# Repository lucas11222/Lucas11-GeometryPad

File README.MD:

# Lucas11 GeometryPad
An HackPad for the popular game Geometry dash. (i love gd colonge)
## Made for Highway (Hackpad)
# Heres a photo of the pcb

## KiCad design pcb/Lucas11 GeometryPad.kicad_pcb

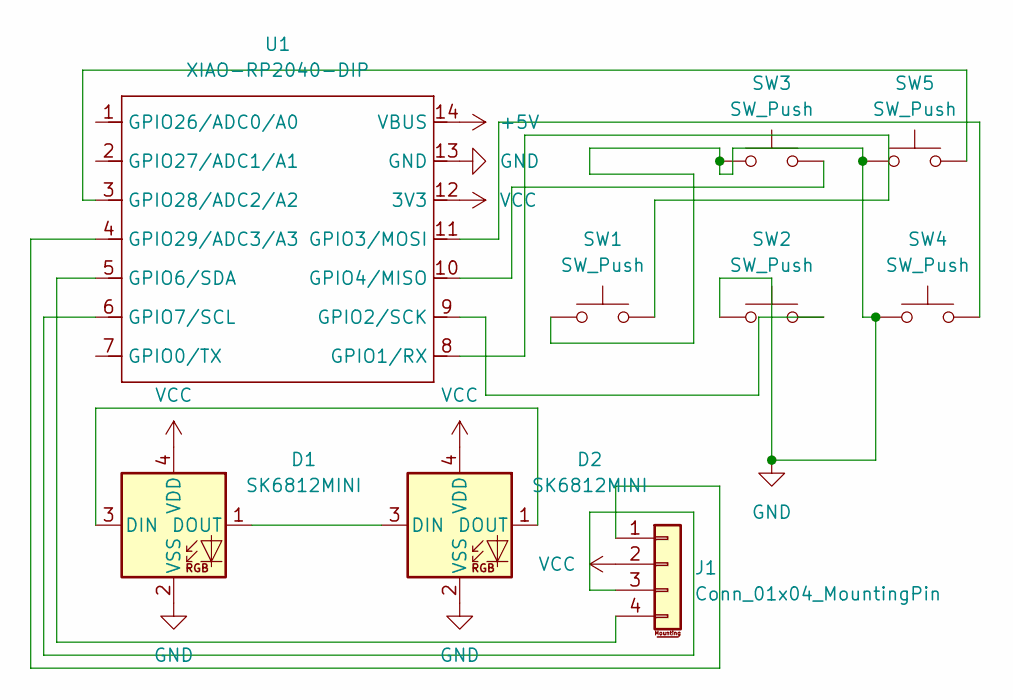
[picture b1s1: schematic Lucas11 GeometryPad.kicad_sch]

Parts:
D1, D2: SK6812MINI; LED_SK6812MINI_PLCC4_3.5x3.5mm_P1.75mm
J1: Conn_01x04_MountingPin; SSD1306-0.91-OLED-4pin-128x32
SW1, SW2, SW3, SW4, SW5: SW_Push; SW_Cherry_MX_1.00u_PCB
U1: XIAO-RP2040-DIP

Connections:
+5V: U1.14 (VBUS)
GND: D1.2 (VSS), D2.2 (VSS), SW1.1, SW2.1, SW3.1, SW4.1, SW5.1, U1.13 (GND)
unnamed: D1.3 (DIN), D2.1 (DOUT)
unnamed: D1.1 (DOUT), D2.3 (DIN)
unnamed: J1.1, U1.4 (GPIO29/ADC3/A3)
unnamed: J1.3, U1.6 (GPIO7/SCL)
unnamed: J1.4, U1.5 (GPIO6/SDA)
unnamed: SW1.2, U1.8 (GPIO1/RX)
unnamed: SW2.2, U1.9 (GPIO2/SCK)
unnamed: SW4.2, U1.11 (GPIO3/MOSI)
unnamed: SW3.2, U1.10 (GPIO4/MISO)
unnamed: SW5.2, U1.3 (GPIO28/ADC2/A2)
VCC: D1.4 (VDD), D2.4 (VDD), J1.2, U1.12 (3V3)

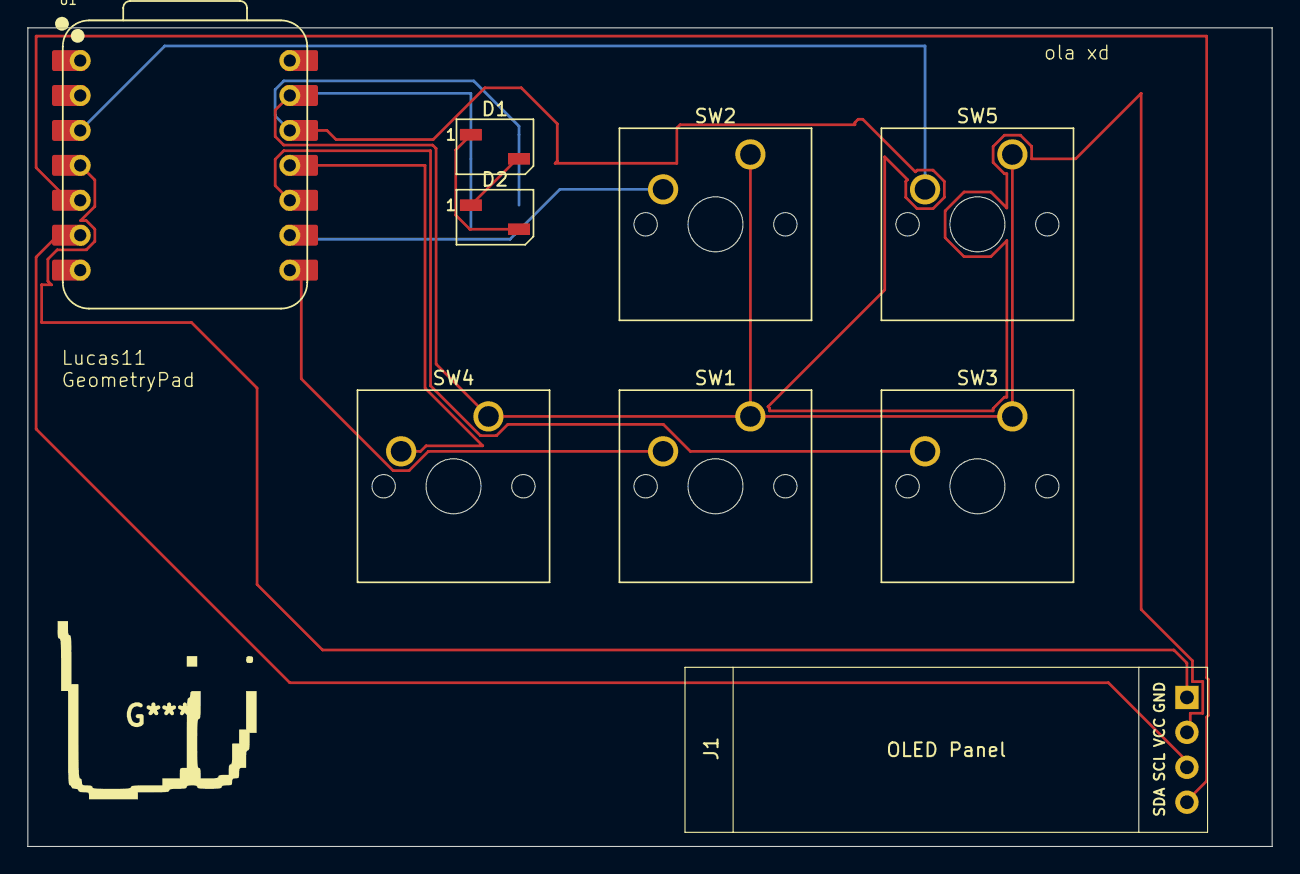
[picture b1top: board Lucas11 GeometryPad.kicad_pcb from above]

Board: 2 copper layers, 90.5 x 59.5 mm, 9 parts (0 on the bottom side), 12 nets.

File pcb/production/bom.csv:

Designator,Footprint,Quantity,Value,LCSC Part #
"D1, D2",LED_SK6812MINI_PLCC4_3.5x3.5mm_P1.75mm,2,SK6812MINI,
J1,SSD1306-0.91-OLED-4pin-128x32,1,Conn_01x04_MountingPin,
"SW1, SW2, SW3, SW4, SW5",SW_Cherry_MX_1.00u_PCB,5,SW_Push,
U1,XIAO-RP2040-DIP,1,XIAO-RP2040-DIP,

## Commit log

2025-05-17 Break
2025-05-17 We are back
2025-05-17 Hello
2025-05-17 Rename cad/lucas11 hackpad case v2.step to Lucas11-GeometryPad.step
2025-05-17 Rename lucas11 hackpad case v2.step to Lucas11-GeometryPad
2025-05-30 Fix some wireing
